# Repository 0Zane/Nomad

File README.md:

# Nomad

**Outdoor embedded device for exploration**

Nomad is a custom outdoor mobile device built around the **ESP32-S3**. It is designed for explorers, researchers, and outdoor enthusiasts who need reliable positioning, long-range communication, environmental awareness, and practical survival utilities in a compact rugged package.
I made this project entirely myself, the idea comes from my passion of making useful objects that help people in specific actions.

> **Project status:** Active development  
> **Last updated:** June 2026

## Documentation

| Resource | Description |
| --- | --- |
| [Nomad Zine](https://github.com/0Zane/Nomad/blob/341650ad904c9da342a7fef04f9b7398d65ead2c/assets/nomadzine.png) | Visual project zine and product-style overview |
| [Bill of Materials](https://github.com/0Zane/Nomad/blob/main/pcb/bom.csv) | Complete component list with quantities and specifications |
| [Main Schematic](https://github.com/0Zane/Nomad/blob/1c8a336e28e47b4648a542668c6f2eea3e4071de/pcb/nomad.svg) | Full board schematic |
| [Module Schematic](https://github.com/0Zane/Nomad/blob/1c8a336e28e47b4648a542668c6f2eea3e4071de/pcb/modules.svg) | Supporting module schematic |

## Table of Contents

- [Project Overview](#project-overview)
- [Key Features](#key-features)
- [Technical Architecture](#technical-architecture)
- [Hardware Design](#hardware-design)
- [Bill of Materials](#bill-of-materials)
- [Firmware](#firmware)
- [Project Structure](#project-structure)
- [License](#license)

## Project Overview

Nomad combines navigation, messaging, sensing, power management, and a custom interface into one portable embedded system.

The device is built for field use, with an emphasis on:

- Knowing where you are through GPS positioning and waypoint tracking.
- Staying connected through long-range LoRa messaging.
- Understanding local conditions through environmental sensing.
- Conserving energy through deep sleep and power-aware firmware.
- Providing simple, fast interaction through buttons and a menu-driven UI.
- Accessing to useful survival tips 
## Key Features

| Feature | What it enables |
| --- | --- |
| **GPS navigation** | Real-time position, coordinates, and waypoint-oriented navigation |
| **LoRa communication** | Long-range SOS alerts, coordinate sharing, and lightweight messages |
| **Environmental monitoring** | Temperature, pressure, and altitude-related readings |
| **Menu-driven UI** | Multi-level navigation built around a clear state-machine structure |
| **Survival tips** | Practical outdoor guidance available directly on the device |
| **Battery optimization** | Deep sleep and intelligent power-management behavior |
| **Custom PCB** | Purpose-built hardware layout for the full Nomad system |
| **Rugged enclosure** | 3D-designed case for portable outdoor use |

## Technical Architecture

### Core Components

| Component | Specification | Interface | Purpose |
| --- | --- | --- | --- |
| **MCU** | ESP32-S3-WROOM-1U | GPIO, UART, SPI, I2C | Main processor running C++ firmware with PlatformIO and Arduino |
| **Display** | 1.9 in IPS ST7789 display panel via FPC | SPI | Smooth UI rendering with menu/submenu screens and PWM brightness control |
| **GPS** | u-blox NEO-M8M | UART | High-precision localization using the TinyGPS++ library |
| **LoRa** | Ebyte E220-900T22S | UART | Long-range messaging for SOS, coordinate sharing, and text packets |
| **Environmental sensor** | BME280 | I2C | Temperature and atmospheric pressure sensing |
| **Input** | 5 buttons with PCF8574T GPIO expander | I2C | Robust button handling with interrupt support |
| **Fuel gauge** | MAX17048G_T10 | I2C | Battery voltage and state-of-charge monitoring |
| **Charger IC** | MCP73831-2-OT | Power management | Li-Po battery charging management |
| **Buck-boost converter** | TPS63060 | Power management | Stable regulated power delivery |
| **Flashlight** | LED | GPIO pin 1 | Controlled illumination for field use |
| **Power source** | Protected Li-ion battery | Power | Main battery with integrated protection circuit |

### Development Stack

| Layer | Tooling |
| --- | --- |
| **Language** | C++ |
| **Framework** | Arduino |
| **Build system** | PlatformIO |
| **IDE** | VS Code with the PlatformIO extension |
| **Primary firmware target** | ESP32-S3 |

## Hardware Design

### Main Schematic

### Module Schematic

### PCB Layout

### 3D Case

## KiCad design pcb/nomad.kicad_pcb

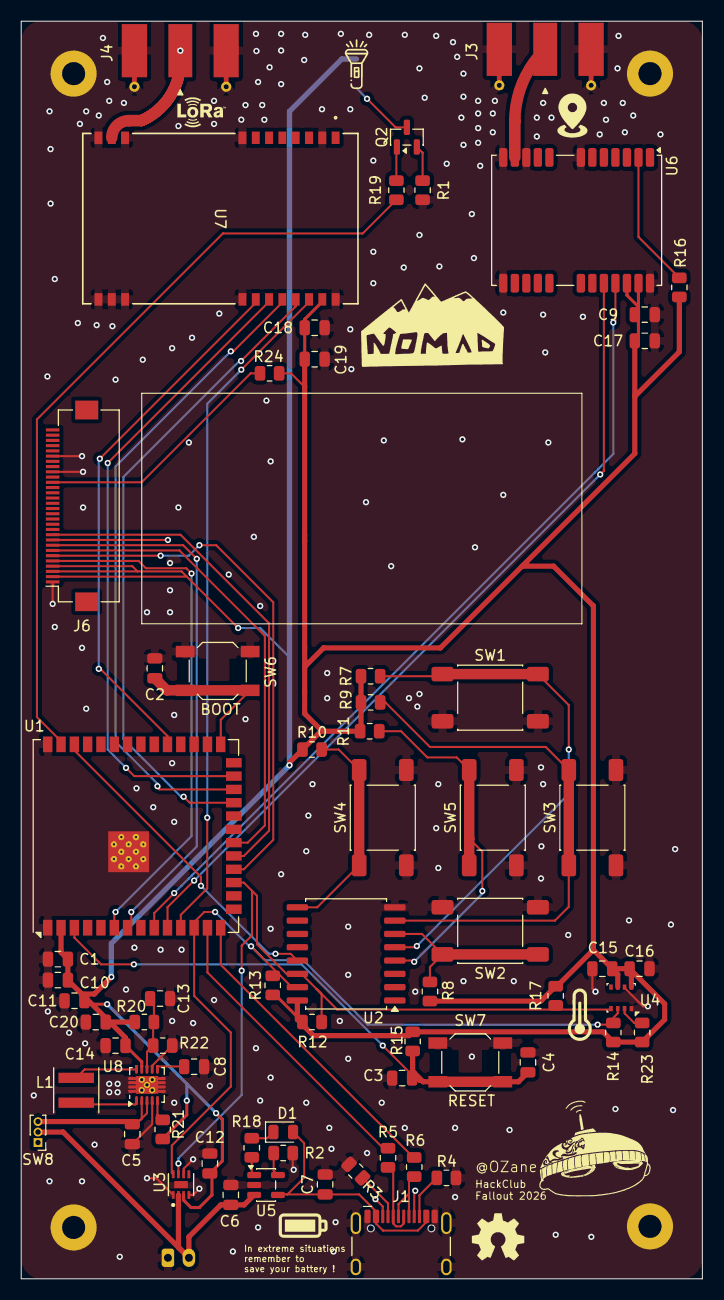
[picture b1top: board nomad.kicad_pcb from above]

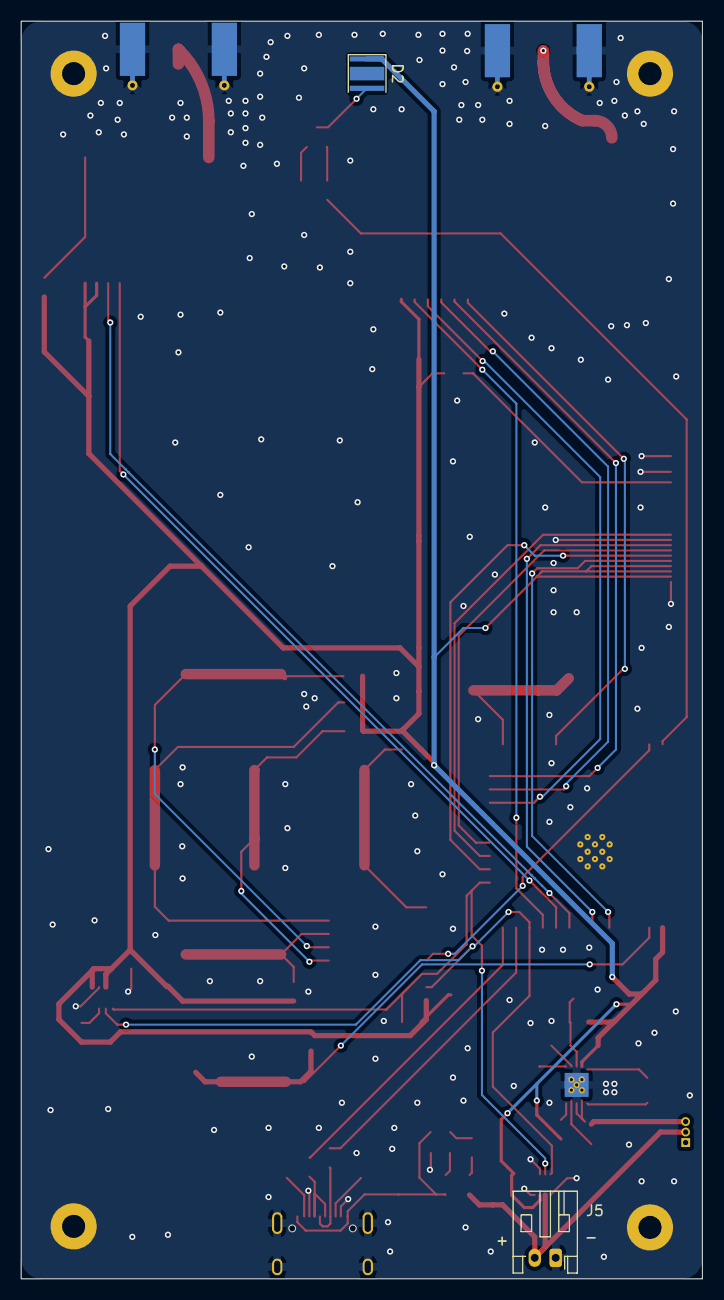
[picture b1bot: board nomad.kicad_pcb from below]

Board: 2 copper layers, 65.0 x 120.0 mm, 69 parts (2 on the bottom side), 50 nets.

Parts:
C1, C2, C3, C4, C8, C9, C12, C15, C16, C18: 0.1uF; C_0805_2012Metric
C5, C10, C11, C14, C20: 22uF; C_0805_2012Metric
C6: C; C_0805_2012Metric
C7: 4.7uF; C_0805_2012Metric
C13: 10pF; C_0805_2012Metric
C17, C19: 10uF; C_0805_2012Metric
D1: LED; LED_0805_2012Metric
D2: LED; LED_Cree-XP-G
J1: USB_C_Receptacle_USB2.0_16P; USB_C_Receptacle_HCTL_HC-TYPE-C-16P-01A
J3, J4: Conn_Coaxial; SMA_Molex_73251-1153_EdgeMount_Horizontal
J5: Conn_01x02_Pin; JST_PH_S2B-PH-K_1x02_P2.00mm_Horizontal
J6: Conn_01x30; Hirose_FH12-30S-0.5SH_1x30-1MP_P0.50mm_Horizontal
L1: 1uH; L_Coilcraft_XxL4020
Q2: 2N7002; SOT-23
R1: 1.5k; R_0805_2012Metric
R2: 2K; R_0805_2012Metric
R3, R4: 5.1k; R_0805_2012Metric
R5, R6: 22R; R_0805_2012Metric
R7, R8, R9, R10, R11, R16: 10k; R_0805_2012Metric
R12, R13, R14, R17: 4.7k; R_0805_2012Metric
R15: R; R_0805_2012Metric
R18: 470R; R_0805_2012Metric
R19: 100R; R_0805_2012Metric
R20: 560k; R_0805_2012Metric
R21: 1M; R_0805_2012Metric
R22: 100k; R_0805_2012Metric
R23: 1K; R_0805_2012Metric
R24: 4.9R +- 0.2R; R_0805_2012Metric
SW1: UP; SW_Push_1P1T_NO_E-Switch_TL3301NxxxxxG
SW2: DOWN; SW_Push_1P1T_NO_E-Switch_TL3301NxxxxxG
SW3: RIGHT; SW_Push_1P1T_NO_E-Switch_TL3301NxxxxxG
SW4: LEFT; SW_Push_1P1T_NO_E-Switch_TL3301NxxxxxG
SW5: SEL; SW_Push_1P1T_NO_E-Switch_TL3301NxxxxxG
SW6, SW7: SW_Push; SW_SPST_SKQG_WithStem
SW8: SW_SPDT; PinHeader_1x03_P1.00mm_Vertical
U1: ESP32-S3-WROOM-1; ESP32-S3-WROOM-1U
U2: PCF8574T; SOIC-16W_7.5x10.3mm_P1.27mm
U3: MAX17048G_T10; SON50P200X200X80-9N
U4: BME280; Bosch_LGA-8_2.5x2.5mm_P0.65mm_ClockwisePinNumbering
U5: MCP73831-2-OT; SOT-23-5
U6: NEO-M8M; ublox_NEO
U7: E220-900T22S; E220-900T22S_BYT
U8: TPS63060; Texas_S-PWSON-N10_ThermalVias

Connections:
+3V3: C1.1, C9.1, C10.1, C11.1, C12.1, C14.2, C15.1, C16.1, C17.1, C18.2, C19.2, C20.1, D2.1 (K), J6.2, J6.3, J6.4, R7.1, R8.1, R9.1, R10.1, R11.1, R12.1, R13.1, R14.1, R15.1, R16.2, R17.1, R20.2, R21.1, R23.1, R24.1, U1.2 (3V3), U2.16 (VDD), U3.3 (VDD), U4.6 (VDDIO), U4.8 (VDD), U6.22 (V_BCKP), U6.23 (VCC), U7.25 (VCC), U8.9 (VOUT)
+5V: C7.1, D1.2 (A), J1.A4 (VBUS), J1.A9 (VBUS), J1.B4 (VBUS), J1.B9 (VBUS), U5.4 (V_{DD})
+BATT: C6.1, J5.2, SW8.2 (B), U3.2 (CELL), U5.3 (V_{BAT})
AUX: U1.11 (IO18), U7.24 (AUX)
BOOT: C2.1, SW6.1, U1.27 (IO0)
BTN_DOWN: R8.2, SW2.1, U2.6 (P2)
BTN_LEFT: R10.2, SW4.1, U2.9 (P4)
BTN_RIGHT: R9.2, SW3.1, U2.7 (P3)
BTN_SEL: R11.2, SW5.1, U2.4 (P0)
BTN_UP: R7.2, SW1.1, U2.5 (P1)
BUTTON_INT: U1.38 (IO2), U2.13 (~INT)
CS: J6.6, U1.18 (IO10)
DC: J6.8, U1.7 (IO7)
FLASHLIGHT: R19.2, U1.39 (IO1)
GND: C1.2, C2.2, C3.2, C4.2, C5.1, C6.2, C7.2, C8.2, C9.2, C10.2, C11.2, C12.2, C13.1, C14.1, C15.2, C16.2, C17.2, C18.1, C19.1, C20.2, J1.A1 (GND), J1.A8 (SBU1), J1.A12 (GND), J1.B1 (GND), J1.B8 (SBU2), J1.B12 (GND), J1.SH (SHIELD), J3.2 (Ext), J4.2 (Ext), J5.1, J6.1, J6.9, J6.22, J6.25, R1.1, R2.2, R3.1, R4.1, R22.2, SW1.2, SW2.2, SW3.2, SW4.2, SW5.2, SW6.2, SW7.2, U1.1 (GND), U1.40 (GND), U1.41 (GND), U2.8 (GND), U3.1 (CTG), U3.4 (GND), U3.6 (QSTRT), U3.9 (EP), U4.1 (GND), U4.7 (GND), U5.2 (V_{SS}), U6.7 (VDD_USB), U6.10 (GND), U6.12 (GND), U6.13 (GND), U6.24 (GND), U7.2 (GND), U7.8 (GND), U7.11 (GND), U7.13 (GND), U7.14 (GND), U7.15 (GND), U7.16 (GND), U7.19 (GND), U7.26 (GND), U8.4 (PS/SYNC), U8.7 (GND), U8.11 (PGND)
GPS MI: U1.10 (IO17), U6.20 (TXD/SPI_MISO)
GPS MO: U1.9 (IO16), U6.21 (RXD/SPI_MOSI)
LORA_MI: U1.23 (IO21), U7.23 (TXD)
LORA_MO: U1.24 (IO47), U7.22 (RXD)
M0: U1.31 (IO38), U7.20 (M0)
M1: U1.25 (IO48), U7.21 (M1)
MOSI: J6.10, U1.19 (IO11)
unnamed: D1.1 (K), R18.1
unnamed: D2.2 (A), Q2.3 (D)
unnamed: J1.A5 (CC1), R3.2
unnamed: J1.B5 (CC2), R4.2
unnamed: J1.A6 (D+), J1.B6 (D+), R6.1
unnamed: J1.A7 (D-), J1.B7 (D-), R5.1
unnamed: J3.1 (In), U6.11 (RF_IN)
unnamed: J4.1 (In), U7.12 (ANT)
unnamed: J6.20, R24.2
unnamed: Q2.1 (G), R19.1
unnamed: Q2.2 (S), R1.2
unnamed: C5.2, SW8.3 (C), U8.2 (VIN), U8.3 (EN)
unnamed: R23.2, U4.2 (CSB)
unnamed: R2.1, U5.5 (PROG)
unnamed: R18.2, U5.1 (STAT)
unnamed: R16.1, U6.2 (D_SEL)
unnamed: C13.2, R20.1, R22.1, U8.8 (FB)
unnamed: L1.2, U8.1 (L1)
unnamed: L1.1, U8.10 (L2)
unnamed: R21.2, U8.5 (PG)
unnamed: C8.1, U8.6 (VAUX)
RES: J6.5, U1.6 (IO6)
RESET: C3.1, C4.1, R15.2, SW7.1, U1.3 (EN)
SCL: R12.2, R17.2, U1.17 (IO9), U2.14 (SCL), U3.7 (SCL), U4.4 (SCK)
SCLK: J6.7, U1.20 (IO12)
SDA: R13.2, R14.2, U1.12 (IO8), U2.15 (SDA), U3.8 (SDA), U4.3 (SDI)
USB_D+: R6.2, U1.14 (USB_D+)
USB_D-: R5.2, U1.13 (USB_D-)

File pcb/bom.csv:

"Reference","Qty","Value","Footprint","Datasheet"
"C1,C2,C3,C4,C8,C9,C12,C15,C16,C18","10","0.1uF","Capacitor_SMD:C_0805_2012Metric",""
"C5,C10,C11,C14,C20","5","22uF","Capacitor_SMD:C_0805_2012Metric",""
"C6","1","C","Capacitor_SMD:C_0805_2012Metric",""
"C7","1","4.7uF","Capacitor_SMD:C_0805_2012Metric",""
"C13","1","10pF","Capacitor_SMD:C_0805_2012Metric",""
"C17,C19","2","10uF","Capacitor_SMD:C_0805_2012Metric",""
"D1","1","LED","LED_SMD:LED_0805_2012Metric",""
"D2","1","LED","LED_SMD:LED_Cree-XP-G",""
"J1","1","USB_C_Receptacle_USB2.0_16P","Connector_USB:USB_C_Receptacle_HCTL_HC-TYPE-C-16P-01A","https://www.usb.org/sites/default/files/documents/usb_type-c.zip"
"J3,J4","2","Conn_Coaxial","Connector_Coaxial:SMA_Molex_73251-1153_EdgeMount_Horizontal",""
"J5","1","Conn_01x02_Pin","Connector_JST:JST_PH_S2B-PH-K_1x02_P2.00mm_Horizontal",""
"J6","1","Conn_01x30","Connector_FFC-FPC:Hirose_FH12-30S-0.5SH_1x30-1MP_P0.50mm_Horizontal",""
"L1","1","1uH","Inductor_SMD:L_Coilcraft_XxL4020",""
"Q2","1","2N7002","Package_TO_SOT_SMD:SOT-23","https://www.onsemi.com/pub/Collateral/NDS7002A-D.PDF"
"R1","1","1.5k","Resistor_SMD:R_0805_2012Metric",""
"R2","1","2K","Resistor_SMD:R_0805_2012Metric",""
"R3,R4","2","5.1k","Resistor_SMD:R_0805_2012Metric",""
"R5,R6","2","22R","Resistor_SMD:R_0805_2012Metric",""
"R7,R8,R9,R10,R11,R16","6","10k","Resistor_SMD:R_0805_2012Metric",""
"R12,R13,R14,R17","4","4.7k","Resistor_SMD:R_0805_2012Metric",""
"R15","1","R","Resistor_SMD:R_0805_2012Metric",""
"R18","1","470R","Resistor_SMD:R_0805_2012Metric",""
"R19","1","100R","Resistor_SMD:R_0805_2012Metric",""
"R20","1","560k","Resistor_SMD:R_0805_2012Metric",""
"R21","1","1M","Resistor_SMD:R_0805_2012Metric",""
"R22","1","100k","Resistor_SMD:R_0805_2012Metric",""
"R23","1","1K","Resistor_SMD:R_0805_2012Metric",""
"R24","1","4.9R +- 0.2R","Resistor_SMD:R_0805_2012Metric",""
"SW1","1","UP","Button_Switch_SMD:SW_Push_1P1T_NO_E-Switch_TL3301NxxxxxG",""
"SW2","1","DOWN","Button_Switch_SMD:SW_Push_1P1T_NO_E-Switch_TL3301NxxxxxG",""
"SW3","1","RIGHT","Button_Switch_SMD:SW_Push_1P1T_NO_E-Switch_TL3301NxxxxxG",""
"SW4","1","LEFT","Button_Switch_SMD:SW_Push_1P1T_NO_E-Switch_TL3301NxxxxxG",""
"SW5","1","SEL","Button_Switch_SMD:SW_Push_1P1T_NO_E-Switch_TL3301NxxxxxG",""
"SW6,SW7","2","SW_Push","Button_Switch_SMD:SW_SPST_SKQG_WithStem",""
"SW8","1","SW_SPDT","Connector_PinHeader_1.00mm:PinHeader_1x03_P1.00mm_Vertical",""
"U1","1","ESP32-S3-WROOM-1","RF_Module:ESP32-S3-WROOM-1U","https://www.espressif.com/sites/default/files/documentation/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"
"U2","1","PCF8574T","Package_SO:SOIC-16W_7.5x10.3mm_P1.27mm","https://www.nxp.com/docs/en/data-sheet/PCF8574_PCF8574A.pdf"
"U3","1","MAX17048G_T10","MAX17048G_T10:SON50P200X200X80-9N",""
"U4","1","BME280","Package_LGA:Bosch_LGA-8_2.5x2.5mm_P0.65mm_ClockwisePinNumbering","https://www.bosch-sensortec.com/media/boschsensortec/downloa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"
"U5","1","MCP73831-2-OT","Package_TO_SOT_SMD:SOT-23-5","http://ww1.microchip.com/downloads/en/DeviceDoc/20001984g.pdf"
"U6","1","NEO-M8M","RF_GPS:ublox_NEO","https://content.u-blox.com/sites/default/files/NEO-M8-FW3_Da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"
"U7","1","E220-900T22S","E220-900T22S_BYT","E220-900T22S"
"U8","1","TPS63060","Package_SON:Texas_S-PWSON-N10_ThermalVias","http://www.ti.com/lit/ds/symlink/tps63060.pdf"

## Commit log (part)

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2026-04-23 Creating firmware environment with PlatformIO
2026-04-23 Adding read temperature feature
2026-04-23 Creating KiCad PCB Project
2026-04-23 Adding gitignore for unwanted KiCad files.
2026-04-23 Adding Flashlight feature
2026-04-23 Fixing pcb project's .gitignore & initializing Kicad project
2026-04-24 Adding a header for each file instead of god header
2026-04-24 Including headers + reading serial commands
2026-04-24 Updating README with prototyping commands
2026-04-25 Adding button read features.
2026-04-26 Setting button pinmodes to input
2026-04-26 Placing MCP9808 symbol
2026-04-26 Programming the MCP9808 (Adafruit MCP9808 library)
2026-04-27 Wiring USB-C, MCP9808, PCF8574T
2026-04-28 Adding gps files
2026-04-29 Programming the PCF8574 I2C Button inputs
2026-04-29 Updating main.cpp
2026-04-29 Writing important informations on pins & modules + todo list in README.md
2026-04-30 Programming GPS module
2026-05-01 Waiting for GPS data buffer to empty before outputting in a while loop,
2026-05-02 Reading INT pin before calling readbutton function
2026-05-02 Adding navigation algorithm
2026-05-03 Replacing temperature sensor schematic + adding INT pin on PCF8574
2026-05-05 Replacing MCP9808 by BME280 sensor
2026-05-05 Writing pins.h and updating every file to access to the pins easily + fixing GPS program
2026-05-06 Adding Lora features
2026-05-08 Adding visual assets
2026-05-08 Correcting readme
2026-05-11 Adding prototyping LoRa pins
2026-05-11 Adding LVGL library
2026-05-13 Adding BOOT & RESET buttons + ESP32 symbol
2026-05-13 Adding voltage divider AMS1117 & USB to UART converter
2026-05-14 Separating modules schematic with system schematic
2026-05-14 Adding elements to their respective location on PCB
2026-05-14 Adding updates to README.md
2026-05-15 Adding battery management system code
2026-05-16 Adding silkscreen icons
2026-05-16 Updating schematic & pcb & BOM
2026-05-18 adding UI library
2026-05-18 Updating PCB
2026-05-19 Updating footprints & shematics + replacing components on PCB
2026-05-19 Wiring MAX17048 battery percentage module
2026-05-19 Adding new modules on README
2026-05-20 Correcting Lora UART communication initialization
2026-05-22 including UI header files
2026-05-22 Updating UI code
2026-05-25 Updating README
2026-05-26 Getting GPS data and returning it tot he main instead of displaying.
2026-05-27 Creating functions that returns each data monitored by the BME280 instead of une function that prints everything in the serial monitor.
2026-05-28 Fixing flashlight function by declaring the name of the argument
2026-05-28 Adding the survival advice function and fixing the getbattery funtion
2026-05-29 Refactoring firmware with libraries and classes inclusions and definitions.
2026-06-01 Fixing firmware
2026-06-01 Fixes on firmware
2026-06-02 Updating firmware
2026-06-03 Adding battery management system with MCP73831 chip.
2026-06-05 Updating footprints, PCb and schematics.
2026-06-05 Updating documentation
2026-06-08 Adding send_gps function to send GPS latitude and longitude on LoRa communication
2026-06-08 Adding ui features
2026-06-10 Add .gitattributes to mark nomadlogo.h as generated
2026-06-11 Updating ui
2026-06-13 Correcting pin conflict
2026-06-13 Updating PCB: Adding Buck boost converter, battery protection and other fixes.
2026-06-14 Updating PCB: Removing battery security and adding slide switch
2026-06-15 Adding NEO-M8N module schematic + BME280 schematic
2026-06-15 Adding LoRa module schematic
2026-06-15 Updating PCB and chainging pin for the LoRa module
2026-06-16 Finishing schematic and updating PCB
2026-06-16 Routing the PCB
2026-06-17 Finishing routing
2026-06-17 Adding 50ohms traces
2026-06-17 Finishing PCB
2026-06-17 Adding bill of materials
2026-06-18 Fixing reversed polarity battery connector
2026-06-18 Adding schematic svg
2026-06-18 Exporting STEP file of PCB
2026-06-18 Updating README adding schematics and BOM
2026-06-19 Replacing screen pins by screen FPC connector
2026-06-19 Updating 3d model
2026-06-20 Updating schematic images
2026-06-20 Adding case 3d models
2026-06-20 Adding BOM
2026-06-20 Uploading PCB gerber file
2026-06-20 Adding zine page
2026-06-20 Adding case image
2026-06-20 Adding zine png file to get permalink
2026-06-20 Updating README for final version with all permalinks and explanations
2026-06-20 Updating gitattributes to ignore icon.h bitmap file (C)
2026-06-20 Uploading pcb layout image to get permalink
2026-06-20 Adding PCB layout image
2026-06-22 Adding assembled project 3d files
2026-06-22 Changing 66uF capacitor to 3* 22uF capacitors
2026-06-22 Updating bom and adding BOM with every price
2026-06-22 Fixing display
2026-06-22 adding " that is breaking the display
2026-06-22 Fixing csv format
2026-06-22 Updating csv format
